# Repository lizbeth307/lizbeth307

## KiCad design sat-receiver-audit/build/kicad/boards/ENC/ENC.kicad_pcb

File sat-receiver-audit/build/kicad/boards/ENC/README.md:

# Дочірня плата енкодера ENC, 24 × 24 мм — W2 PCB-SB1

**Статус: `SB1_ROUTED_NOT_FOR_FABRICATION`.** Один дизайн для ENC301 (головний енкодер, екземпляр ENCM) і ENC302 (гучність, ENCV) плюс одна запасна плата — 3 плати. Плату розведено в `sr-rx-pcb` (KiCad 10.0.7, Freerouting 2.5.0; прогін розведення 43129454692 на 00ae328 — повторне розведення на смузі wip/w2-int після злиття B2B: входи ті самі, аудит межі тепер рахує J208/J209; результат той самий, що в прогоні 42421671986 на 87d332d): DRC — помилок 0, непідключених 0, 7 переглянутих попереджень `silk_over_copper` (контур PEC11R перетинає власні площадки), `ignored_checks` порожній; аудит source-pad — 0 для ENCM і ENCV; аудит межі — `provisional: header ref pending GR-3` (нижче). Це результат CI/моделі, а не випуск у виробництво й не апаратний PASS.

- **Від пілота W2 PCB-PIPE** без змін лишилися контур і два отвори з контракту механіки, PEC11R на (12, 12) з кутом 90, скриптовий заблокований зв'язок GND J1.1 → ENC.C на B.Cu і заливки GND; S1/S2 кнопки несуть кола графа (E3_ENCx_PRESS_EXT і GND, W2 GR-1).
- **J1 — площадка для дротів, роз'єм не ставиться.** Кінці S37/S38 — чотири дроти 26 AWG (Alpha Wire 5853), впаяні в 4-контактну площадку з кроком 2.0 мм (KiCad PinHeader_1x04_P2.00mm_Vertical: отвір 0.8, площадка 1.35) у крайовій зоні зліва; порядок GND, A, B, PRESS — як у J316/J317 на CTRL, де стоїть корпус PH 4. Рішення «Роз'єм плати ENC (W2 PCB-SB1)», build/15: жоден корпус JST PH не вміщується поруч із PEC11R на 24 × 24.
- **OPEN:** позиції графа для площадки J1 ще немає (`design/E3.json`, лінія GR), тож J1 лишається `pilot_placeholder`, аудит межі — `provisional`, а в BOM JLC рядок J1 має позначку TBD (деталь не ставиться). Ref з доменом ENC має з'явитися разом з відображенням J1 у `pcb/boards/ENC.json` і заміною синтезованих кінців X37S0-ENCM/X38S0-ENCV; тест `test_enc_keeps_the_acceptance_string` (`pcb/tests/test_board_gen.py`) тоді треба замінити новим. `pcb/rules/jlc-2l.kicad_dru` не підключено (`rules_file` лишається `null`). Кріплення — build/17 F29 (довжина TBD), висоти — модель механіки.

Файли: специфікація `../../../../pcb/boards/ENC.json`; проєкт `ENC.kicad_pro`; виходи прогону `[pcb-route ENC]` (плата, `report.json`, `drc.json`, `connectors.json`, `route-log.json`, SVG, `fp-lib-table`), `review.json` і `fab/` — лише патчем `pcb-regenerated-ENC` у коміті `GENERATED:`.

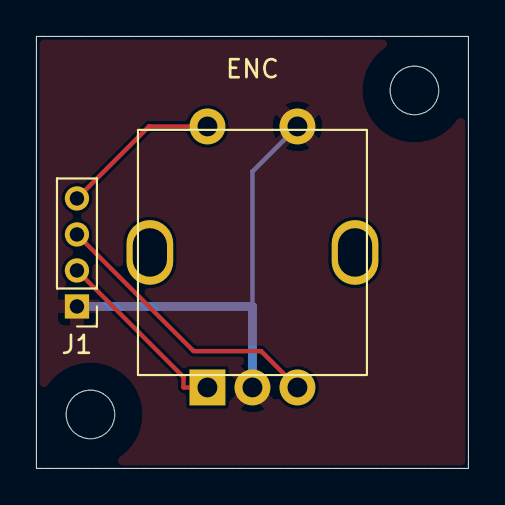
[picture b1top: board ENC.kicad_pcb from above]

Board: 2 copper layers, 24.0 x 24.0 mm, 4 parts (0 on the bottom side), 4 nets.

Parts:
ENC: PEC11R-4220F encoder; RotaryEncoder_Bourns_PEC11R-4xxxF-Sxxxx
H1, H2: NPTH_2.7mm
J1: S37/S38 wire land, no part fitted; PinHeader_1x04_P2.00mm_Vertical

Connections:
ENC_A: ENC.A, J1.2
ENC_B: ENC.B, J1.3
ENC_SW: ENC.S1, J1.4
GND: ENC.C, ENC.S2, J1.1

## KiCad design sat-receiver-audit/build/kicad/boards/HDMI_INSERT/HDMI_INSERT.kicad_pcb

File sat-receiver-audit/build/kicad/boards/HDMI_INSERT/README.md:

# Вставка HDMI_INSERT, 16 × 18 мм — W2 PCB-SB2 (контур і розміщення; гнізда FPC — OPEN)

**Статус: `SB2_ROUTED_MECH_FIT_OPEN_NOT_FOR_FABRICATION`.** Плату розміщено й розведено в `sr-rx-pcb` (KiCad 10.0.7, Freerouting 2.5.0; прогін розведення 43129454692 на 00ae328 — повторне розведення на смузі wip/w2-int після злиття B2B: входи ті самі, аудит межі тепер рахує J208/J209; результат той самий, що в прогоні 43111813288 на e7c7763f, лише відрізків 40 замість 41): DRC — помилок 0, непідключених 0, попереджень 4 (лише шовкографія), `ignored_checks` порожній; аудит source-pad — 0 помилок; аудит меж — **`provisional: FPC socket ref pending GR-4 (Adafruit 3548/3550/3560 FPC pinout and socket MPN unpublished)`**; `pcb/check_boards.py` — 0 знахідок. Це результат CI/моделі, не випуск у виробництво: на цьому етапі плата — лише острів контакту 18 (+5 V) між двома гніздами FPC, тест лінії HDMI лишається OPEN.

## Що на платі і чого немає

- **Є (граф E5):** U506 LM66100 (ідеальний діод +5 V контакту 18 з боку Q6A до дисплея), C517 і C518 (100 нФ на вході й виході), R552 (підтяжка ST_N), TP502 (діагностика ST_N).
- **Заглушки J1 / J2** (KiCad 10.0.7 `Connector_PinHeader_2.00mm:PinHeader_1x02_P2.00mm_Vertical`, sha256 з gitlab 10.0.7, перевіряється з копією образу під час прогону): місце гнізда A (нижній край, гнучкий шлейф 1 від Q6A: E5_HDMI_5V_Q6A і GND) і гнізда B (верхній край, шлейф 2 до плати HDMI дисплея: E5_HDMI_5V_DISP і GND). На них нічого не ставиться; у JLC BOM вони — рядки `TBD`.
- **Немає:** гнізд FPC і всього набору кіл проходження (TMDS ×3, CLK, DDC, CEC, HPD, екрани): Adafruit не публікує розводку й MPN гнізд для 3548/3550/3560 (W2 GR-4, сторінки прочитано 07.11.2026), тож будь-яке призначення контактів було б вигадкою.

## Розташування

Координати — мм, початок у точці корпусу (210.5, 34.0), осі паралельні осям корпусу, y угору; контур = резерв `hdmi_insert` W2 MECH-4 (x 210.5–226.5, y 34–52, z 40.5–45.5). Плата лежить на лицьовій грані пластини на поліімідній стрічці й поролоновому скотчі (низ z 41.59 — припущення: стрічку для цього з'єднання ще не названо), без отворів; деталі ≤ 2.3 мм над платою (`contract-proposal.json`).

## Рішення й відкрите

- Рішення плану (build/15 «HDMI_INSERT — прохідна плата (W2 PCB-SB2)»): друкована прохідна плата між двома сегментами FPC. Кінцева плата — 4 шари JLC04161H-7628, TMDS 100 Ом диференційно, вирівняні за довжиною, U506/C517/C518/R552/TP502 на контакті 18 (constraints.json IO-01). Поточні 2 шари — лише для острова живлення.
- OPEN (лінія GR / власник): MPN і розводка гнізд FPC (вимір «продзвонкою» пари адаптерів зі шлейфом або дані від Adafruit), позиції гнізд у `design/E5.json`, повний набір кіл; потім — 4-шаровий стек, розміщення гнізд на місці J1/J2 і `[pcb-route HDMI_INSERT]`. Механіка — запис у `mechanical/params/boards.json`.

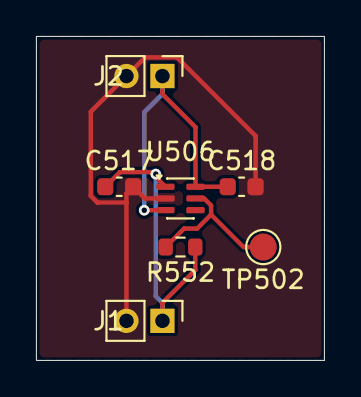
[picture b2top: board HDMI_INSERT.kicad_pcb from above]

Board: 2 copper layers, 16.0 x 18.0 mm, 7 parts (0 on the bottom side), 4 nets.

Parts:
C517, C518: 100nF X7R 10V; C_0603_1608Metric
J1: FPC socket A placeholder (pin 18 in, GND), nothin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; PinHeader_1x02_P2.00mm_Vertical
J2: FPC socket B placeholder (pin 18 out, GND), nothi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; PinHeader_1x02_P2.00mm_Vertical
R552: 100k 1%; R_0603_1608Metric
TP502: HDMI ideal diode ST_N diagnostic; TestPoint_Pad_D1.5mm
U506: LM66100DCKR HDMI5V ideal diode; SOT-363_SC-70-6

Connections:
E5_HDMI_5V_DISP: C518.1, J2.1, U506.3, U506.6
E5_HDMI_5V_Q6A: C517.1, J1.1, R552.2, U506.1
E5_HDMI_ST_N: R552.1, TP502.1, U506.5
GND: C517.2, C518.2, J1.2, J2.2, U506.2

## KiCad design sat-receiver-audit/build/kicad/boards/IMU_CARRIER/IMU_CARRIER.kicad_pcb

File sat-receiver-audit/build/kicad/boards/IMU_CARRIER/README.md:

# Носійна плата паку IMU — IMU_CARRIER — W2 PCB-SB2

**Статус: `SB2_ROUTED_MECH_FIT_OPEN_NOT_FOR_FABRICATION`.** Прогін розведення 43129454692 на 00ae328 (`sr-rx-pcb`, KiCad 10.0.7, Freerouting 2.5.0; повторне розведення на смузі wip/w2-int після злиття B2B: входи ті самі, аудит межі тепер рахує J208/J209; результат той самий, що в прогоні 43115230745 на 01d14323): DRC — помилок 0, непідключених 0, попереджень 20 (лише шовкографія), `ignored_checks` порожній; аудит source-pad — 0 помилок; аудит меж — `pass`; 32 заблоковані сегменти збережено; `pcb/check_boards.py` — 0 знахідок (1 запис `unverified`: кількість перехідних отворів на перехід PWR1A — порада, не перевірка). Результат CI/моделі, не випуск у виробництво; посадка в пак і ворота IMU-01 лишаються OPEN.

## Контур (пропозиція)

Координати — мм, початок у точці коробки Hammond 1550Z101 (2.0, 0.5) за `mechanical/params/imu_pack.json`, осі паралельні осям коробки, y угору. Смуга 40.28 × 6.0 з `imu_pack.json` carrier_pcb не вміщує 16 майданчиків W2 GR-4 з кроком 4 мм і 8 деталей, тож плата складається з трьох частин (`contract-proposal.json`):

- **смуга** x 0–40.28, y 0–5.9 — резерв carrier_pcb, на 0.1 нижча біля шестигранників стійок BNO085;
- **язик** x 6.0–16.5, y 5.9–11.5 — під BNO085 між її двома передніми стійками; на ньому лише підтяжки R390/R391 і C341 (без струму живлення під магнітометром);
- **рукав** x 25.0–40.28, y 5.9–14.5 — під RP2040-Zero (стійок для неї не вибрано; стовпчик друкованого носія моделі під її кутом — OPEN нижче), на 6.7 мм від осі штативної вставки 1/4-20.

Отвори ⌀3.2 на (4.0, 3.5) і (36.28, 3.5) — гвинти M3 носія (коробка (6.0, 4.0) і (38.28, 4.0), build/17 F35), зона без міді ⌀6.0. Стійки BNO085 — Würth 970130155 (AI-STANDOFF-IMU-13), поза платою.

## Розміщення й мідь

- **Смуга, нижній ряд (y 1.5):** J321 (поворот 180°: TX 20, RX 16, CS 12, WAKE 8) до RP2040-Zero; J320 (поворот 180°: VIN 31.5, GND 27.5, 3V3 23.5).
- **Смуга, верхній ряд (y 4.4):** J322 (поворот 180°: 3V3 24.6, GND 20.6, CS 16.6, WAKE 12.6, 3V3 8.6) до BNO085; праворуч — C519.
- **Рукав:** J518 (y 7.5: 5V 26.5, GND 30.5, TX 34.5, RX 38.5) — жили кабелю IMU; над ним C340, C520, D502 і TVS U552.
- **Мідь:** скриптові заблоковані E5_IMU_VIN (0.4 мм, F.Cu: катод D502 → C340/C520/C519 → J320.1), E5_IMU5V (0.35 мм — ширина PWR1A, по B.Cu з двома переходами до анода D502 і U552.3), IMU_TX / IMU_RX (по B.Cu у проміжку рядів до J321, короткі F.Cu відводи до U552). Роутер розводить CS, WAKE, 3V3 і GND; заливки GND з обох боків з прямим приєднанням.
- Висоти: найвища деталь — D502 SMA 2.3 ≤ parts_h 2.5 (`imu_pack.json`, припущення лінії IMU).

## Відкрито (OPEN)

- Лінія IMU: контур у `imu_pack.json` (і `mechanical/params/boards.json`), стос гвинтів M3 через дно, друкований носій і плату (fastener-stacks IMU-CARRIER), кріплення RP2040-Zero (отворів немає), орієнтація BNO085 у парі (тут — бік 22.86 уздовж x, припущення).
- **Друкований носій (механіка й лінія IMU):** модель `mechanical/srrx_mech/cad_fixtures.py:112-116` (`mechanical/generated/stl/imu_carrier.stl`) ставить чотири стовпчики ⌀5.0 × 13 мм на кути пари — коробка (4.3, 9.3), (40.0, 9.3), (4.3, 29.9) і (40.0, 29.9). Стовпчик (40.0, 9.3) під кутом RP2040-Zero стоїть у рукаві: перекриває кортиярди J518 (центр майданчика RX — за 1.39 мм від осі) і U552 (2.19 мм); на правому передньому отворі BNO085 (22.12, 9.34) стовпчика немає. Стовпчики мають перейти на отвори BNO085 (коробка x 4.34 / 22.12, y 9.34 / 29.66 за припущенням орієнтації) або поступитися стійкам Würth AI-STANDOFF-IMU-13, а кріплення RP2040-Zero — оминути рукав; інакше рукав дістає виріз, J518 і U552 переносять, і плату один раз перерозводять (`[pcb-route IMU_CARRIER]`).
- **Орієнтація BNO085 (механіка):** креслення I-01 (`mechanical/srrx_mech/antennas.py:294`) малює BNO085 стороною 25.6 уздовж x, а пара 40.7 = 22.7 + 18 (`components/adafruit_bno085_4754_rp2040_zero_metal_p.md:34`) кладе вздовж x сторону 22.7, як ця плата. За орієнтацією I-01 права передня стійка стала б на (24.66, 9.34), і її шестигранник (до x 27.55) зайшов би в рукав на 0.55 мм.
- Посадка, IMU-01 і всі ворота паку — стенд.

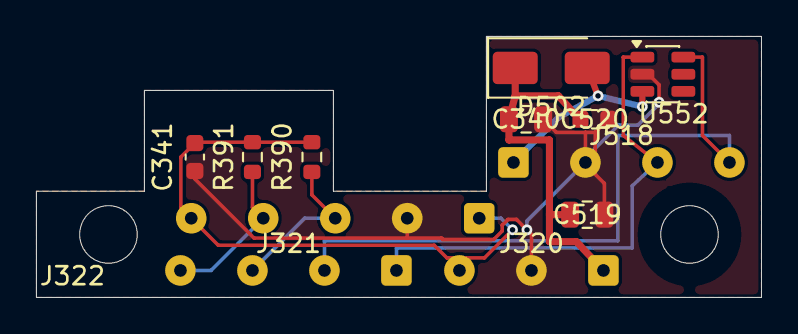
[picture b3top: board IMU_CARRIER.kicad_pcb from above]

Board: 2 copper layers, 40.3 x 14.5 mm, 14 parts (0 on the bottom side), 8 nets.

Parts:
C340: 10u 10V; C_0805_2012Metric
C341: 100n 16V; C_0603_1608Metric
C519: 10uF X7R 10V; C_0805_2012Metric
C520: 100nF X7R 10V; C_0603_1608Metric
D502: SS14-E3/61T IMU supply reverse isolation; D_SMA
H1, H2: NPTH_3.2mm
J320: Майданчики живлення RP2040-Zero U309 на IMU_CARRI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; SolderWire-0.15sqmm_1x03_P4mm_D0.5mm_OD1.5mm
J321: Майданчики сигналів RP2040-Zero U309 на IMU_CARRI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; SolderWire-0.15sqmm_1x04_P4mm_D0.5mm_OD1.5mm
J322: Майданчики BNO085 U314 на IMU_CARRIER; SolderWire-0.15sqmm_1x05_P4mm_D0.5mm_OD1.5mm
J518: Майданчики кабелю IMU HELU 49655 на IMU_CARRIER; SolderWire-0.15sqmm_1x04_P4mm_D0.5mm_OD1.5mm
R390: 10k; R_0603_1608Metric
R391: 1k; R_0603_1608Metric
U552: TPD4E1U06DBVR; SOT-23-6

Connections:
E3_IMU3V3: C341.1, J320.3, J322.1, J322.5, R390.2, R391.2
E3_IMU_CS_N: J321.3, J322.3, R390.1
E3_IMU_WAKE_N: J321.4, J322.4, R391.1
E5_IMU5V: D502.2, J518.1, U552.3
E5_IMU_VIN: C340.1, C519.1, C520.1, D502.1, J320.1
GND: C340.2, C341.2, C519.2, C520.2, J320.2, J322.2, J518.2, U552.2
IMU_RX: J321.2, J518.4, U552.6
IMU_TX: J321.1, J518.3, U552.1

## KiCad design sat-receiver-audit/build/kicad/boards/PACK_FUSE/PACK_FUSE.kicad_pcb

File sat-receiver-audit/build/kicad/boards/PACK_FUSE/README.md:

# Носій запобіжника паку PACK_FUSE, 10.7 × 26.4 мм — W2 PCB-SB2

**Статус: `SB2_ROUTED_MECH_FIT_OPEN_NOT_FOR_FABRICATION`.** Плату розміщено й «розведено» в `sr-rx-pcb` (KiCad 10.0.7, Freerouting 2.5.0; прогін розведення 43111813288 на e7c7763f): DRC — помилок 0, непідключених 0, попереджень 2 (лише шовкографія: `silk_over_copper`, `silk_overlap`), `ignored_checks` порожній; аудит source-pad — 0 помилок; аудит меж — `pass`; незалежна перевірка `pcb/check_boards.py` — 0 знахідок. Це результат CI/моделі, а не випуск у виробництво й не апаратний PASS; механічне припасування і нагрів при 7.5 A лишаються OPEN.

## Файли

| Файл | Що це |
|---|---|
| `../../../../pcb/boards/PACK_FUSE.json` | специфікація плати для `pcb/board_gen.py` і `pcb/check_boards.py` |
| `contract-proposal.json` | контур, отвори, зона без міді, висоти й розташування в корпусі — **пропозиція** W2 PCB-SB2 з джерелами; у контракті механіки (`mechanical/generated/contract/boards.json`) плати PACK_FUSE ще немає |
| `PACK_FUSE.kicad_pro` | проєкт KiCad: рівні перевірок DRC (набір HATCH/ENC) і клас `SCRIPTED_BATT` (3.2 мм) для E1_CELL4 і E1_SHUNT_P |
| `PACK_FUSE.kicad_pcb`, `report.json`, `drc.json`, `connectors.json`, `route-log.json`, `PACK_FUSE-top.svg`, `PACK_FUSE-bottom.svg`, `fp-lib-table`, `review.json`, `fab/` | виходи прогону `[pcb-route PACK_FUSE]` (§2: лише патчем `pcb-regenerated-PACK_FUSE` у коміті `GENERATED:`); `fab/` — набір `pcb/fab_export.py` (NOT RELEASED) |

## Розташування

Координати плати — мм, початок у точці корпусу (161.7, 11.5), осі паралельні осям корпусу, y угору. Плата лежить на двох стійках PEM SO-M2.5-6ZI 6 мм на розширенні пластини (M-07 PF1–PF2, `mechanical/params/mechanical.json` module_mounts pack_fuse): низ плати z 46.5, верх 48.1; верхній бік (F) з тримачем дивиться до лицьової стінки (+z).

- **Контур:** = конверт `pack_fuse_board` W2 MECH-5 (x 161.7–172.4, y 11.5–37.9).
- **Отвори:** ⌀2.7 на (7.3, 2.6) і (7.3, 23.8) = корпус (169.0, 14.1) і (169.0, 35.3); зона без міді ⌀5.0 на обох шарах — головка гвинта (dk 4.5) і бочка стійки (C 4.20) мають потенціал пластини. Кріплення — build/17 F39.
- **Тримач Keystone 3568 (F101):** уздовж плати, контакт 1 (E1_CELL4) — до J116; центр тіла (5.35, 13.2) = центр конверта `pack_fuse` (тримач 7.37 + запобіжник MINI 8.8 = 16.17 над платою).
- **J116 / J117:** майданчики проводу 18 AWG (1 мм², отвір 1.75) біля торців: J116 (2.4, 2.6) — провід від BT104.+, J117 (2.4, 23.8) — S05-02 до J105.2 на PWR-A; висота кінця з пайкою — до 1.9 над платою (конверт `pack_fuse_board` до z 50.0).
- **Мідь:** обидва кола — клас BATT (4.6 A тривало, 7.5 A F101; 3.2 мм на одному зовнішньому шарі 1 oz): скриптові заблоковані доріжки 3.2 мм на F.Cu і B.Cu від майданчика до обох площадок контакту тримача плюс суцільні заливки половини плати на обох шарах з прямим приєднанням площадок. Роутер нічого не розводить (клас `SCRIPTED_BATT` у `router.ignore_net_classes`).
- **Ізоляція:** нижній бік (виводи тримача, J116/J117) після пайки — під поліімідною стрічкою (build/17 F39); під платою 3.8 мм над бусинкою NTC корпусу TH302.

## Відкрито (OPEN)

- Запис PACK_FUSE у `mechanical/params/boards.json` і контракт механіки за цією пропозицією; потім специфікація посилається на контракт і плату один раз перерозводять (`[pcb-route PACK_FUSE]`).
- Нагрів міді й контакту тримача при 7.5 A, момент гвинтів F39 (купон) — стенд.
- Позиція F-0297007.5-WXNV у БД деталей описує запобіжник (LCSC C178942); тримач Keystone 3568 — «extra» цієї позиції, окремого рядка JLC BOM для THT-тримача немає (власник БД деталей).

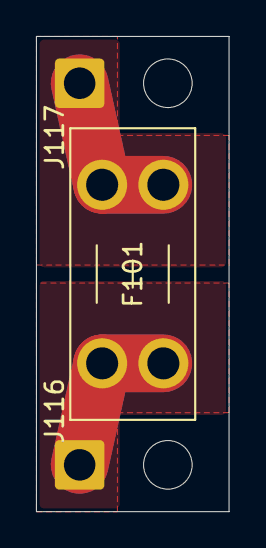
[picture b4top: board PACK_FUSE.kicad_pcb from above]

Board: 2 copper layers, 10.7 x 26.4 mm, 5 parts (0 on the bottom side), 2 nets.

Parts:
F101: Mini-blade 7.5 A DC ≥32 V; Fuseholder_Blade_Mini_Keystone_3568
H1, H2: NPTH_2.7mm
J116: Майданчик проводу 18 AWG: вхід F101 від BT104.+; SolderWire-1sqmm_1x01_D1.4mm_OD2.7mm
J117: Майданчик проводу 18 AWG: вихід F101 у S05; SolderWire-1sqmm_1x01_D1.4mm_OD2.7mm

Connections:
E1_CELL4: F101.1, J116.1
E1_SHUNT_P: F101.2, J117.1

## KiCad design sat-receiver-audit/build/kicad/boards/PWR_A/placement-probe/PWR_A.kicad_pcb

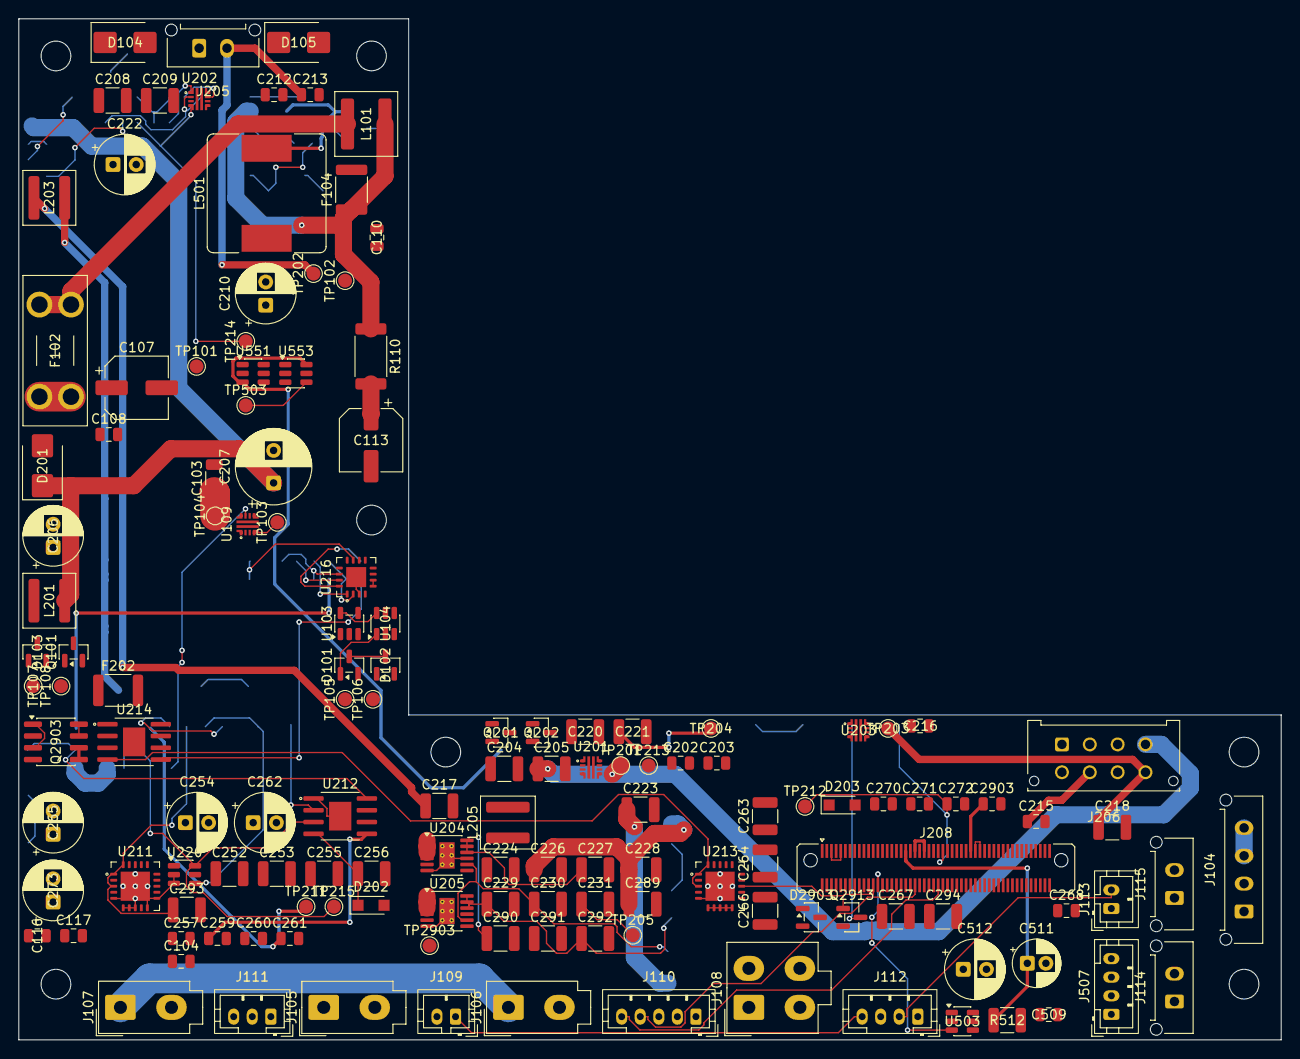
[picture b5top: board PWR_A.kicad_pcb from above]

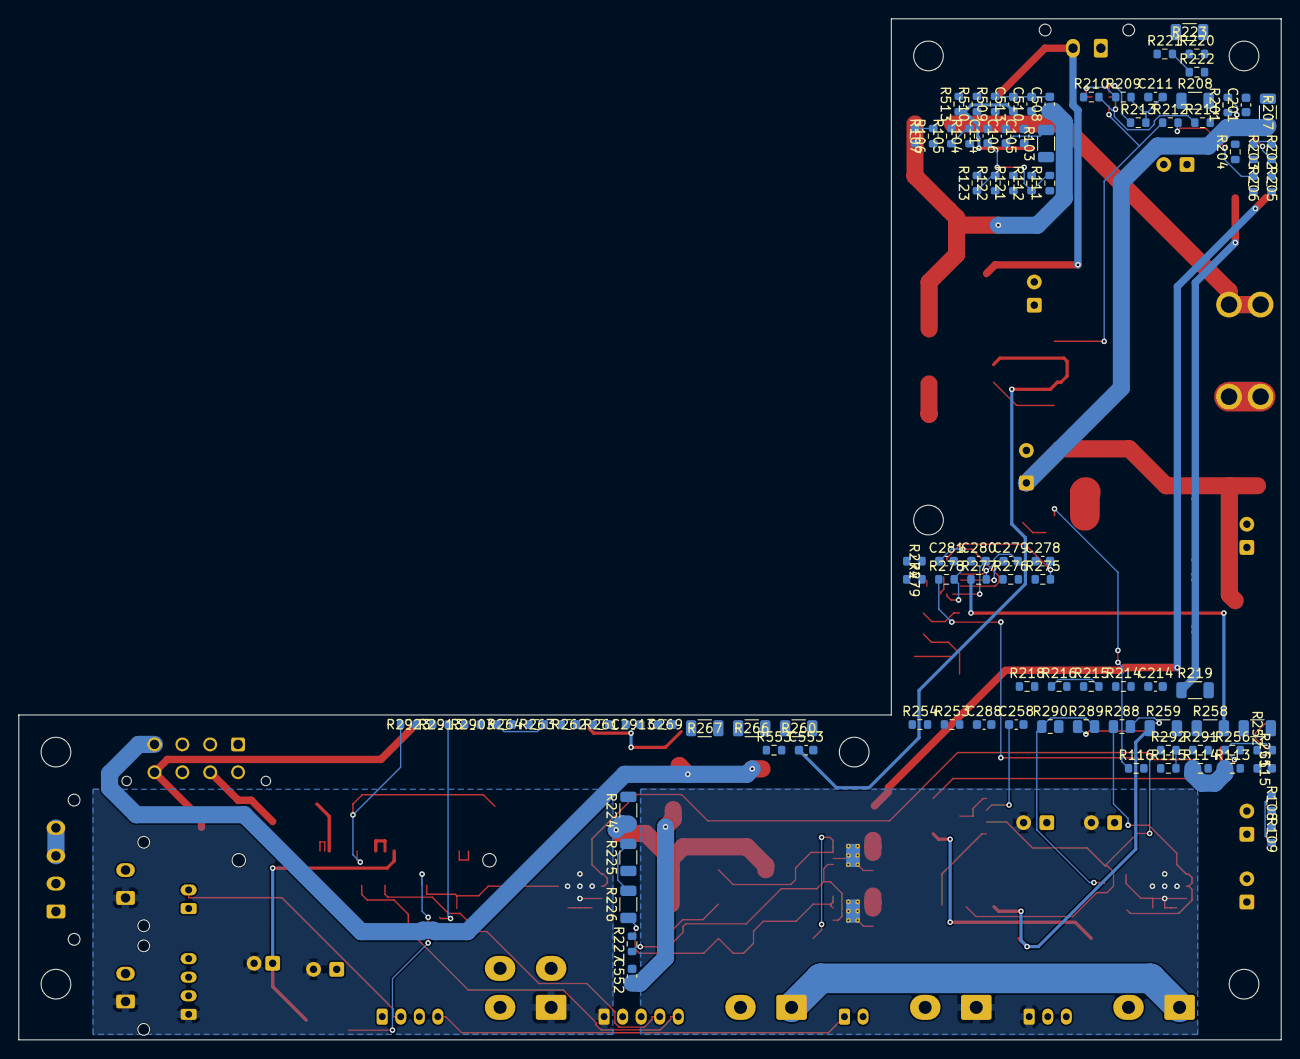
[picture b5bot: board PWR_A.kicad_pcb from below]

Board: 4 copper layers, 136.0 x 110.0 mm, 242 parts (94 on the bottom side), 129 nets.

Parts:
C103: 2.2µF50VX7R (effective≥1µF); C_1206_3216Metric
C104: 4.7µF10VX7R (effective≥2.2µF); C_0805_2012Metric
C105, C106: 100nF10VX7R; C_0603_1608Metric
C107: 100µF35VlowESR; CP_Elec_6.3x7.7
C108, C110, C116, C117: 1µF50VX7R; C_0805_2012Metric
C113: 16SVPC100M 100 µF 16 V ±20% OS-CON; CP_Elec_6.3x5.9
C114: 100nF10V; C_0603_1608Metric
C115: 3.3nF50VC0G; C_0603_1608Metric
C201, C211, C214: 3.3nF 50V C0G C1608C0G1H332J080AA; C_0603_1608Metric
C202, C203, C212, C213, C215, C216, C257, C259, C260, C261, C268, C270, C271, C272, C2903: 1uF 50V X7R C2012X7R1H105K125AB; C_0805_2012Metric
C204, C205, C208, C209, C217, C218, C220, C221, C226, C228, C230, C252, C253, C255, C263, C264, C266, C289, C291: 10uF 50V X7R C3225X7R1H106K250AC; C_1210_3225Metric
C206, C210, C222, C254, C262, C265, C273: 47uF 50V EEUFR1H470; CP_Radial_D6.3mm_P2.50mm
C207: 220uF/25V UHE1E221MPD; CP_Radial_D8.0mm_P3.50mm
C223, C224, C227, C229, C231, C256, C267, C290, C292, C293, C294: 22uF 50V X7R C3225X7R1H226M250AC; C_1210_3225Metric
C258: 47nF 50V X7R C1608X7R1H473K080AA; C_0603_1608Metric
C269, C278, C279, C280, C281, C288, C2913: 100nF 50V X7R C1608X7R1H104K080AA; C_0603_1608Metric
C508, C513, C552: 100nF X7R 10V; C_0603_1608Metric
C509: 4.7uF X7R 10V; C_0805_2012Metric
C510, C553: 1uF X7R 10V; C_0603_1608Metric
C511: EEU-FR1C101 100uF 16V; CP_Radial_D5.0mm_P2.00mm
C512: 220uF 16V low-ESR; CP_Radial_D6.3mm_P2.50mm
D101, D102, D103: BAT54,215; SOT-23
D104, D105: SMBJ17A-E3/52; D_SMB_KA
D201: SMBJ13A-E3/52; D_SMB_KA
D202, D203: PMEG4030ER; Nexperia_CFP3_SOD-123W
D2903: BZX84C10-7-F; SOT-23
F102: 4 A DC ≥32 V LAB5; Fuseholder_Blade_Mini_Keystone_3568
F104, F202: MF-MSMF075/24-2 0.75A; Fuse_1812_4532Metric
H1, H2, H3, H4, H5, H6, H7: NPTH_3.2mm
J104: X02P1-PWR: Molex Micro-Fit 3.0 4, верхній вхід, S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; Molex_Micro-Fit_3.0_43650-0415_1x04_P3.00mm_Vertical
J105: X05J1-PWR: Molex Mini-Fit Jr. 2×1, верхній вхід, 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; Molex_Mini-Fit_Jr_5566-02A_2x01_P4.20mm_Vertical
J106: X06J1-PWR: Molex Mini-Fit Jr. 2×1, верхній вхід, 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; Molex_Mini-Fit_Jr_5566-02A_2x01_P4.20mm_Vertical
J107: X07J1-PWR: Molex Mini-Fit Jr. 2×1, верхній вхід, 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; Molex_Mini-Fit_Jr_5566-02A_2x01_P4.20mm_Vertical
J108: X10J1-PWR: Molex Mini-Fit Jr. 2×2, верхній вхід, 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; Molex_Mini-Fit_Jr_5566-04A_2x02_P4.20mm_Vertical
J109: X05S1-PWR: JST PH 2, верхній вхід, S05; JST_PH_B2B-PH-K_1x02_P2.00mm_Vertical
J110: X06S1-PWR: JST PH 5, верхній вхід, S06; JST_PH_B5B-PH-K_1x05_P2.00mm_Vertical
J111: X07S1-PWR: JST PH 3, верхній вхід, S07; JST_PH_B3B-PH-K_1x03_P2.00mm_Vertical
J112: X10S1-PWR: JST PH 4, верхній вхід, S10; JST_PH_B4B-PH-K_1x04_P2.00mm_Vertical
J113: X11S1-PWR: JST PH 2, верхній вхід, S11; JST_PH_B2B-PH-K_1x02_P2.00mm_Vertical
J114: X11P1-PWR: Molex Micro-Fit 3.0 2, верхній вхід, S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; Molex_Micro-Fit_3.0_43650-0215_1x02_P3.00mm_Vertical
J115: X12P1-PWR: Molex Micro-Fit 3.0 2, верхній вхід, S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; Molex_Micro-Fit_3.0_43650-0215_1x02_P3.00mm_Vertical
J205: X19P1-PWR: Molex Micro-Fit 3.0 2, верхній вхід, S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; Molex_Micro-Fit_3.0_43650-0215_1x02_P3.00mm_Vertical
J206: SL2-PWR-MF: Molex Micro-Fit 3.0 2×4, верхній вхід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; Molex_Micro-Fit_3.0_43045-0812_2x04_P3.00mm_Vertical
J208: B2B-PWRA: Samtec LSHM-150 2×50, PWR-A верх, стик 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; Samtec_LSHM-150-xx.x-x-DV-N_2x50_P0.50mm_Vertical
J507: X32S1-PWR: JST PH 4, верхній вхід, S32; JST_PH_B4B-PH-K_1x04_P2.00mm_Vertical
L101: XAL6060-103MEC 10 µH ±20%; L_Coilcraft_XAL6060-XXX
L201, L203, L205: 1uH XAL5030-102MEC; L_Coilcraft_XAL5030-XXX
L501: SRR1260-101M 100uH; L_Bourns_SRR1260
Q101: 2N7002,215; SOT-23
Q201: AO3407A; SOT-23
Q202, Q2913: 2N7002; SOT-23
Q2903: DMP6050SSD-13; SOIC-8_3.9x4.9mm_P1.27mm
R103: 3.30M0.1%25ppm; R_1206_3216Metric
R104: 332k0.1%25ppm; R_0603_1608Metric
R105: 4.02k0.1%25ppm TRIM; R_0603_1608Metric
R106, R111, R123: 100k1%; R_0603_1608Metric
R107: 4.22M1%; R_0603_1608Metric
R108: 4.99k0.1%25ppm; R_0603_1608Metric
R109: 562R0.1%25ppm; R_0603_1608Metric
R110: WSL2512R3300FEA 0.330 Ω 1%; R_2512_6332Metric
R112: 20.0k1%; R_0603_1608Metric
R113: 470k1%; R_0603_1608Metric
R114: 174k0.1%; R_0603_1608Metric
R115: 10.0k0.1%; R_0603_1608Metric
R116: 953Ω1%; R_0603_1608Metric
R121: 2.20k1%; R_0603_1608Metric
R122: 1.00k1%; R_0603_1608Metric
R201, R213, R218, R220, R253, R261, R292, R2903: 100k 1%; R_0603_1608Metric
R202: 13.0k 1% 100ppm; R_0603_1608Metric
R203: 825R 1%; R_0603_1608Metric
R204, R210: 102k 0.1%; R_0603_1608Metric
R205, R211, R216: 10.0k 0.1%; R_0603_1608Metric
R206, R212, R221, R222, R2923: 10.0k 1%; R_0603_1608Metric
R207, R208, R219, R223, R224, R252, R259, R260, R267: 0.22R 1% 0.25W; R_1206_3216Metric
R209: 1.96k 1%; R_0603_1608Metric
R214: 1.65k 1%; R_0603_1608Metric
R215: 19.6k 0.1%; R_0603_1608Metric
R225, R226: 20mR 1% 0.25W; R_1206_3216Metric
R227: 21.5k 0.1% 25ppm; R_0603_1608Metric
R254: 2.05k 1%; R_0603_1608Metric
R255: 110k 0.5%; R_0603_1608Metric
R256: 10.0k 0.5%; R_0603_1608Metric
R258: 0.100R 0.1% 0.25W Kelvin; R_1206_3216Metric
R262: 7.15k 1% 100ppm; R_0603_1608Metric
R263: OVLO TBD (start 102k 0.1%); R_0603_1608Metric
R264: OVLO TBD (start 9.09k 0.1%); R_0603_1608Metric
R266: 0.200R 0.1% 0.25W Kelvin; R_1206_3216Metric
R274, R275, R276, R277, R278, R279: 10.0R 1%; R_0603_1608Metric
R288: TNPW0805332KBYEA 332k 0.1%10ppm; R_0805_2012Metric
R289: TNPW08052K00BYEA 2.00k 0.1%10ppm; R_0805_2012Metric
R290: TNPW080510K0BYEA 10.0k 0.1%10ppm; R_0805_2012Metric
R291: 4.70k 1%; R_0603_1608Metric
R509: RILIM TBD (start 28.7k 1%); R_0603_1608Metric
R510: 100k; R_0603_1608Metric
R512: 1Ohm 0.5W; R_1210_3225Metric
R513: 10k; R_0603_1608Metric
R553: RILIM TBD (start 88.7k 1%); R_0603_1608Metric
R2913: 22k 1%; R_0603_1608Metric
TP101: PG_SYS12резерв; TestPoint_Pad_D1.5mm
TP102: PG_LAB5резерв; TestPoint_Pad_D1.5mm
TP103: PD_FLT service; TestPoint_Pad_D1.5mm
TP104: ВузолN; TestPoint_Pad_D1.5mm
TP105: ВузолSW; TestPoint_Pad_D1.5mm
TP106: AON3V3; TestPoint_Pad_D1.5mm
TP107: Protectedground; TestPoint_Pad_D1.5mm
TP108: UV_OFF; TestPoint_Pad_D1.5mm
TP201: J21; TestPoint_Pad_D1.5mm
TP202: DISP12; TestPoint_Pad_D1.5mm
TP203: LIME3V3; TestPoint_Pad_D1.5mm
TP204: AUX12; TestPoint_Pad_D1.5mm
TP205: LNA4V5; TestPoint_Pad_D1.5mm
TP211: LNB13V2; TestPoint_Pad_D1.5mm
TP212: BONI13V8; TestPoint_Pad_D1.5mm
TP213: E2_FAULT_J21; TestPoint_Pad_D1.5mm
TP214: E2_FAULT_DISP; TestPoint_Pad_D1.5mm
TP215: OVP_LNB_N; TestPoint_Pad_D1.5mm
TP503: IMU 5V switch FAULT_N test point; TestPoint_Pad_D1.5mm
TP2903: BONI13V8_PORT; TestPoint_Pad_D1.5mm
U103: TPS70933DBVR; SOT-23-5
U104: MCP65R41T-1202E/CHY; SOT-23-6
U109: TPS259470ARPWR USB-C; TI_RPW0010A_VQFN-HR-10_2x2mm_P0.5mm
U201, U202, U203: TPS259470ARPWR; TI_RPW0010A_VQFN-HR-10_2x2mm_P0.5mm
U204, U205: LT3045EMSE#PBF; MSOP-12-1EP_3x4.039mm_P0.65mm_EP1.651x2.845mm_ThermalVias
U211, U213: TPS7A4701RGWT; TI_RGW0020A_VQFN-20-1EP_5x5mm_P0.65mm_EP3.15x3.15mm
U212, U214: TPS259630DDAR; TI_DDA0008_HSOP-8-1EP_3.9x4.9mm_P1.27mm_EP2.4x3.1mm
U216: INA3221AIRGVR; TI_RGV0016A_VQFN-16-1EP_4x4mm_P0.65mm_EP2.16x2.16mm
U220: TPS3701DDCR; TSOT-23-6
U503: TPS2553DBVR-1; SOT-23-6
U551: TPD4E1U06DBVR; SOT-23-6
U553: TPS2553DBVR; SOT-23-6

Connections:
3V3_Q6A: C281.1, J208.1, R206.2, R212.2, U216.4, U216.16
AON3V3: C104.1, C105.1, J110.2, TP106.1, U103.5, U104.6
AUX12: C221.1, J208.61, R223.1, TP204.1
AUX12_DAMP: C222.1, R223.2
BONI13V8: C272.1, J208.53, Q2903.7, Q2903.8, R267.1, R2923.1, TP212.1
BONI13V8_DAMP: C273.1, R267.2
BONI13V8_PORT: C2903.1, J208.65, Q2903.5, Q2903.6, TP2903.1
CHG_INHIBIT: J208.18, R122.1
DISP12: C213.1, J205.2, TP202.1, U202.6
E1_BAT_ADC: C114.1, J208.20, R111.2, R112.1
E1_CHG_CC1: J112.1, J113.1
E1_CHG_CC2: J112.2, J113.2
E1_CHG_GATE: Q101.1, R122.2, R123.1
E1_CHG_INHIBIT_LOW: J112.3, Q101.3, R121.2
E1_CHG_NTC: J109.1, J112.4, R121.1
E1_EN_SYS12: R108.2, R109.1
E1_LAB5_DAMP: C113.1, R110.2
E1_LAB5_FUSED: F102.2, L101.1
E1_MASTER_OFF: D101.3, D102.3, J111.2
E1_N: C103.1, D104.K, J106.1, J107.1, J108.2, R103.1, TP104.1, U103.1
E1_PD_DVDT: C115.1, U109.7
E1_PD_EN: R113.2, U109.1
E1_PD_FLT: TP103.1, U109.4
E1_PD_ILM: R116.1, U109.9
E1_PD_OVLO: R114.2, R115.1, U109.2
E1_SHUNT_P: J105.2, J106.2
E1_SW: C107.1, C108.1, C110.1, C252.1, C263.1, C288.1, D105.K, J107.2, R108.1, R111.1, TP105.1, U220.5
E1_SWITCH_A: D103.1, J111.3
E1_USB_PD_RAW: C116.1, J114.2, R113.1, R114.1, U109.5
E1_USB_PD_SAFE: C117.1, J108.3, U109.6
E1_UV_OFF: D101.1, R107.1, TP108.1, U104.1
E1_UV_REF: R106.1, U104.5
E1_UV_REFH: R106.2, R107.2, U104.3
E1_UV_SENSE: C106.1, R103.2, R104.1, U104.4
E1_UV_TRIM: R104.2, R105.1
E2_AUX_GATE: Q201.1, R221.2, R222.1
E2_AUX_GSINK: Q202.3, R222.2
E2_AUX_PTC: C220.1, F202.2
E2_AUX_SWITCHED: F202.1, Q201.3
E2_BLKB_G: C2913.2, D2903.1, Q2903.2, Q2903.4, R2903.2, R2913.1
E2_BLKB_S: C2913.1, D2903.3, Q2903.1, Q2903.3, R2903.1
E2_BLKB_SINK: Q2913.3, R2913.2
E2_BONI_DVDT: C269.1, U214.2
E2_BONI_EF: C270.1, R266.1, R278.1, U214.5
E2_BONI_ILM: R262.1, U214.7
E2_BONI_IN: C264.1, C266.1, R260.1, U213.15, U213.16
E2_BONI_IN_DAMP: C265.1, R260.2
E2_BONI_LDO: C267.1, C294.1, D203.1, R263.1, U213.1, U213.3, U213.20, U214.4
E2_BONI_MON: C271.1, R266.2, R279.1
E2_BONI_NR: C268.1, U213.14
E2_BONI_OV: R263.2, R264.1, U214.8
E2_DISP_IN: C209.1, C212.1, R208.1, R210.1, U202.5
E2_DISP_IN_DAMP: C210.1, R208.2
E2_FAULT_DISP: R212.1, TP214.1, U202.4
E2_FAULT_J21: R206.1, TP213.1, U201.4
E2_J21_EF: C203.1, C204.1, L201.1, U201.6
E2_J21_EN: R201.2, R202.1, U201.1
E2_J21_FUSED: C202.1, R201.1, R204.1, U201.5
E2_LIME_EF: C216.1, C217.1, L203.1, U203.6
E2_LNA4_SHUNT: J208.100, R275.1
E2_LNA4_SW: J208.99, R274.1
E2_LNA_IN: C224.1, C226.1, C228.1, C289.1, C291.1, L205.2, R224.1, U204.1, U204.2, U204.3, U204.4, U204.7, U205.1, U205.2, U205.3, U205.4, U205.7
E2_LNA_SET: C230.1, R227.1, U204.8, U205.8
E2_LNB_DVDT: C258.1, U212.2
E2_LNB_EF: C259.1, R258.1, R276.1, U212.5
E2_LNB_ILM: R254.1, U212.7
E2_LNB_IN: C253.1, C255.1, R252.1, U211.15, U211.16
E2_LNB_IN_DAMP: C254.1, R252.2
E2_LNB_LDO: C256.1, C293.1, D202.1, R255.1, R288.1, U211.1, U211.3, U211.20, U212.4
E2_LNB_MON: C260.1, R258.2, R277.1
E2_LNB_NR: C257.1, U211.14
E2_LNB_OV: R255.2, R256.1, U212.8
E2_LNB_OV_DIV_MID: R288.2, R289.1
E2_LNB_PRECISE_SENSE: R289.2, R290.1, U220.4
E2_LT_OUT1: C227.1, C290.1, R225.1, U204.10, U204.11, U204.12
E2_LT_OUT2: C229.1, C292.1, R226.1, U205.10, U205.11, U205.12
E2_U201_DVDT: C201.1, U201.7
E2_U201_ILM: R203.1, U201.9
E2_U201_OV: R204.2, R205.1, U201.2
E2_U202_DVDT: C211.1, U202.7
E2_U202_ILM: R209.1, U202.9
E2_U202_OV: R210.2, R211.1, U202.2
E2_U203_DVDT: C214.1, U203.7
E2_U203_ILM: R214.1, U203.9
E2_U203_OV: R215.2, R216.1, U203.2
E2_U216_IM1: C278.2, R275.2, U216.11
E2_U216_IM2: C279.2, R277.2, U216.14
E2_U216_IM3: C280.2, R279.2, U216.1
E2_U216_IP1: C278.1, R274.2, U216.12
E2_U216_IP2: C279.1, R276.2, U216.15
E2_U216_IP3: C280.1, R278.2, U216.2
E5_HFP_DAMP: C512.1, R512.2
E5_IMU5V: C553.1, J507.2, U551.3, U553.6
E5_IMU_FAULT: TP503.1, U553.4
E5_U503_ILIM: R509.1, U503.5
E5_U553_ILIM: R553.1, U553.5
E5_VBUS_HFP_SW: C510.1, L501.1, U503.6
EN_AUX12: J208.22, Q202.1, R220.1
EN_BONI: J208.24, Q2913.1, R261.1, U213.13, U214.3
EN_HFP: J208.26, R510.1, U503.3
EN_LIME3V3: J208.28, R218.1, U203.1
EN_LNB: J208.30, R253.1, R291.1, U211.13
FAULT_HFP: J208.32, U503.4
FLT_BONI: J208.34, U214.6
FLT_LIME3V3: J208.36, U203.4
FLT_LNB: J208.38, U212.6
GND: C103.2, C104.2, C105.2, C106.2, C107.2, C108.2, C110.2, C113.2, C114.2, C115.2, C116.2, C117.2, C201.2, C202.2, C203.2, C204.2, C205.2, C206.2, C207.2, C208.2, C209.2, C210.2, C211.2, C212.2, C213.2, C214.2, C215.2, C216.2, C217.2, C218.2, C220.2, C221.2, C222.2, C223.2, C224.2, C226.2, C227.2, C228.2, C229.2, C230.2, C231.2, C252.2, C253.2, C254.2, C255.2, C256.2, C257.2, C258.2, C259.2, C260.2, C261.2, C262.2, C263.2, C264.2, C265.2, C266.2, C267.2, C268.2, C269.2, C270.2, C271.2, C272.2, C273.2, C281.2, C288.2, C289.2, C290.2, C291.2, C292.2, C293.2, C294.2, C508.2, C509.2, C510.2, C511.2, C512.2, C513.2, C552.2, C553.2, C2903.2, D104.A, D105.A, D201.A, D202.2, D203.2, J104.1, J104.2, J105.1, J108.1, J110.1, J111.1, J114.1, J115.1, J205.1, J206.1, J206.3, J206.5, J206.7, J208.3, J208.4, J208.7, J208.8, J208.11, J208.12, J208.15, J208.16, J208.19, J208.23, J208.27, J208.31, J208.35, J208.39, J208.43, J208.47, J208.51, J208.55, J208.59, J208.63, J208.67, J208.69, J208.97, J208.98, J507.1, Q101.2, Q202.2, Q2913.2, R105.2, R109.2, R112.2, R115.2, R116.2, R123.2, R202.2, R203.2, R205.2, R209.2, R211.2, R213.2, R214.2, R216.2, R218.2, R220.2, R227.2, R253.2, R254.2, R256.2, R261.2, R262.2, R264.2, R290.2, R292.2, R509.2, R510.2, R513.2, R553.2, R2923.2, TP107.1, U103.2, U104.2, U109.8, U201.8, U202.8, U203.8, U204.6, U204.9, U204.13, U205.6, U205.9, U205.13, U211.5, U211.6, U211.7, U211.8, U211.10, U211.11, U211.EP, U212.1, U212.EP, U213.5, U213.6, U213.7, U213.8, U213.9, U213.10, U213.EP, U214.1, U214.EP, U216.3, U216.EP, U220.2, U220.3, U503.2, U551.2, U553.2
I2C0_SCL: J110.3, J208.40
I2C0_SDA: J110.4, J208.42
I2C2_SCL: J208.44, U216.5, U216.6
I2C2_SDA: J208.46, U216.7
IMU_RX: J208.48, J507.3, U551.6
IMU_TX: J208.50, J507.4, U551.1
INA228_ALERT: J110.5, J208.52
J21: C205.1, C207.1, D201.K, J206.4, L201.2, R207.1, TP201.1
J21_DAMP: C206.1, R207.2
LAB5: C223.1, C508.1, C509.1, C552.1, F104.1, J104.3, J104.4, J206.2, J208.2, J208.6, J208.10, J208.14, L101.2, L205.1, R110.1, U503.1, U553.1, U553.3
LAB5_RLY: F104.2, J208.41, J208.45
LIME3V3: C218.1, J206.8, L203.2, R219.1, TP203.1
LNA4V5: C231.1, J208.5, J208.9, R225.2, R226.2, TP205.1
LNB13V2: C261.1, J208.57, R259.1, TP211.1
LNB13V2_DAMP: C262.1, R259.2
OVP_LNB_N: J208.54, R291.2, R292.1, TP215.1, U212.3, U220.6
PICO_DISP_EN: J208.56, R213.1, U202.1
PICO_OFF: D102.1, J208.58
PWR_BUTTON: D103.3, J208.60
SYS12: C208.1, Q201.2, R221.1
VBUS_HFP: C511.1, C513.1, J208.37, L501.2, R512.1, R513.1
VCC_3V3_MKEY: C215.1, J206.6, R215.1, U203.5
